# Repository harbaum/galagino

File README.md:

# Galagino - ESP32 Arcade Emulator

Play Galaga, Pac-Man, Donkey Kong, Frogger, Digdug and 1942 on the ESP32

## New and improved versions

Since Galagino was started in 2023 many developers have updated
and improved this project and these successors have long left this
original Galagino behind.

I recommend you check the following versions as well:

  * [GalaginoPlus](https://github.com/VirtualClaudioBoy/GalaginoPlus) featuring an impressive 43 games and most other third party contributions
  * [Speckhoilers Galagino](https://github.com/speckhoiler/galagino) increasing the number of supported games to 30!!
  * [Galagino3](https://github.com/SurvivalHacking/galagino3) adding several new games, supporting an OLED for the marquee and enhancing joystick support as well as adding new games
  * [Another Galagino](https://github.com/galagino/galagino) adding new games and support for more display types
  * ... and various other great ports and contributions ...

## Original Galagino from 2023

[Pac-Man](https://en.wikipedia.org/wiki/Pac-Man),
[Galaga](https://en.wikipedia.org/wiki/Galaga) and
[Donkey Kong](https://en.wikipedia.org/wiki/Donkey_Kong_(video_game)) are three of the most
iconic arcade machines of all times and are listed on places #1 to #3
on the [Killer List of Video Games](http://www.klov.net).

Especially Pac-Man and Galaga have been remade and emulated many
times. So far the cheapest and smallest system able to do a faithful
emulation of the original arcade machines was the raspberry pi. But
even the much cheaper ESP32 should be able to easily emulate a machine
from the early ’80s, shouldn't it?

Well, things are not that easy. The Galaga arcade was driven by three
Z80 CPUs, each running at 3Mhz. Additionally the arcade machine
included two more CPUs, one for button and coin handling and one for audio
support. And finally the hardware itself had dedicated support
for simple wavetable audio, tilemap graphics and up to 64 sprites.
The video resultion was 224 by 288 pixels.

The ESP32 on the other hand
comes with two cores running at 240MHz. But it lacks dedicated video
hardware. Emulating the various CPUs as well as the handling of
audio and graphics turned out to be challenging for the ESP32.

Cheap TFT screens with a resolution of 320 by 240 pixels are avaialable
in various sizes from 2.0 inch to 3.2 inch allowing for a very small
and cheap *galagino* setup.

These small displays usually allow for SPI clock rates of up to 40MHz
allowing for a max screen refresh rate of ~30Hz. This is exactly half
the refresh rate of the original arcade machine. 30Hz is sufficient
for a very fluid gameplay. However, with displays coping with 80MHz
SPI clock, Galagino will run at full 60Hz refresh.

## Youtube videos

* [First Galaga Emulation test ](https://www.youtube.com/shorts/LZRI6izM8XM)
* [Sound and Starfield working](https://www.youtube.com/shorts/8uNSv0aRtgY)
* [Galaga is finally playable](https://www.youtube.com/shorts/wqnJzOAAths)
* [Pac-Man on Galagino](https://www.youtube.com/shorts/F4-XiiPwG1c)
* [Donkey Kong on Galagino](https://www.youtube.com/shorts/KROFJ0Rtj0w)
* [Boot menu](https://www.youtube.com/shorts/_PJyn06yrtg)
* [Cardboard cabinet prototype](https://youtube.com/shorts/vverV4NphlQ)
* [Finished plywood cabinet](https://youtube.com/shorts/a3-wctRAIds)
* [John Bradnam's 3D printed case](https://www.youtube.com/watch?v=p29Yvht4jSI)
* [Frogger on Galagino](https://youtube.com/shorts/LrBkN1pu7yE)
* [Digdug on Galagino](https://youtube.com/shorts/fmQmfKEhVy4)

## Hardware

### Original Hardware
The hardware is built around one of those cheap ESP32 development
boards like the ESP32 Devkit V4 depicted in the images below. The
components needed for the breadboard setup are listed below. If you
plan to build the [cabinet](hardware/cabinet) instead you might want
to make sure you [order the exact parts](./hardware) that
aren't only electrically compatible but also mechanically.

* ESP32 development board (e.g. [Devkit V4](https://www.espressif.com/en/products/devkits/esp32-devkitc))
* A 320x240 SPI TFT screen (no touch needed)
  * Either a ILI9341 based screen as depicted, or
  * a ST7789 based screen with 320x240 pixels
* An audio amplifier and speaker
  * e.g. a [PAM8302A](https://www.adafruit.com/product/2130) and a 3W speaker (as seen in the photos), or
  * a [Keyestudio SC8002B](https://www.keyestudio.com/products/keyestudio-sc8002b-audio-power-amplifier-speaker-module-for-arduino-player), or similar 
* five push buttons, or
* one push button and a five way joystick breakout (for Pac-Man and Donkey Kong)
* breadboard and wires

The entire setup should be connected as depicted below. The Devkit is
too wide for the breadboard leaving no space above it to connect
wires. Thus the wires going to the top pin row of the Devkit are
placed underneath the DevKit with the connections done as shown in the
image below. See [galagino/config.h](galagino/config.h) for the button
mappings.

[PDF](images/galagino_bb.pdf)

This setup with five buttons works fine for Galaga since there is no
vertical movement in the game that requires a joystick. A joystick is
needed for Pac-Man and Donkey Kong. The joystick based setup would
then be wired in the following way:

[PDF](images/galagino_5way_bb.pdf)

### "Cheap Yellow Display"
The ESP32-2432S028R A.K.A. the [Cheap Yellow Display](https://github.com/witnessmenow/ESP32-Cheap-Yellow-Display) is an ESP32 Board that comes with the majority of hardware required to build a Galagino device.

Hardware Needed:
- Cheap Yellow Display
- [A Nintendo Wii nunchuck and adaptor](hardware/NUNCHUCK.MD) - This can be connected to the JST connector labled "CN1" with the cable included with the display
- (or) a [Nintento Switch Pro Controller](hardware/BLUEPAD32.MD) or [similar](https://github.com/ricardoquesada/bluepad32)
- A speaker - This can be attached to the display with a 1.25mm JST connector to the connector labled "SPEAK" (or soldered)

Note: The `Start` button is connected to the "boot" button on the board.

To get the project working on the Cheap Yellow Display, just uncomment the `#define CHEAP_YELLOW_DISPLAY_CONF` line in [galagino/config.h](galagino/config.h)

## Software

**Important notice 1:** You really need to use the Arduino IDE as it
provides the optimization settings required for sufficient
perfgormance of Galaga and Digdug by default. E.g. PlatformIO doesn't
seem to enable enough optimization.

**Important notice 2:** I2S/DAC support seems to be [broken in the
ESP32 board package version 2.0.10 and
up](https://github.com/espressif/arduino-esp32/issues/8467). Please
use ESP32 board package 2.0.9 or older for a clean sound.

The software consists of three parts:

* The [Galagino specific code](galagino/) contained in this repository
* The orignal ROM files
    * [Galaga (Namco Rev. B ROM)](https://www.bing.com/search?q=galaga+namco+b+rom)
    * [Pac-Man (Midway)](https://www.bing.com/search?q=pacman+midway+arcade+rom)
    * [Donkey Kong (US set 1)](https://www.bing.com/search?q=donkey+kong+arcade+rom)
    * [Frogger](https://www.bing.com/search?q=frogger+arcade+rom)
    * [Digdug](https://www.bing.com/search?q=digdug+arcade+rom)
    * [1942](https://www.bing.com/search?q=1942+arcade+rom)	
* A [Z80 software emulation](https://fms.komkon.org/EMUL8/Z80-081707.zip) by [Marat Fayzullin](https://fms.komkon.org/)

Galagino uses code that is not freely available and thus not included in this
repository. Preparing the firmware thus consists of a few additional steps:

* The ROM files have to be placed in the [roms directory](roms/), together with the ZIP file containing the Z80 emulator.
* A set of [python scripts](romconv/) is then being used to convert and
 patch the ROM data and emulator code and to include the resulting code into the
galagino sketch directory.
* The same scripts are afterwards being used to convert [audio sample files](./samples) into the desired format.

The [ROM conversion](./romconv) as well as the [audio sample
conversion](./samples) create a whole bunch of additional files in the
[galagino directory](./galagino). Please check the README's in the
[romconv](./romconv) and [samples](./samples) directories for further
instructions.

With all these files in place, the galagino.ino sketch can be loaded
into the [Arduino IDE](https://docs.arduino.cc/software/ide-v2). The
Arduino IDE must have the [ESP32 board support](https://docs.espressif.com/projects/arduino-esp32/en/latest/installing.html)
installed and the appropriate board like e.g. the
*ESP32 Dev Module* should be selected. Finally the default core used
by Arduino should be 1 (this is the default) as Galagino will use core 0
for audio and video emulation. Furthermore the FastLED library should
be installed to support the LEDs in the [cabinets marquee](./hardware/cabinet).
LED support can be disabled in the configuration if no LEDs are going to be installed.

## Configuration

The Galagino code can be configured through the [galagino/config.h](galagino/config.h)
file. This is also the place where it's possible to choose between the ILI9341
controller (default) and the ST7789.

Also the pin assignment can be adjusted as well as the TFT SPI clock or the
use of LEDs for the marquee.

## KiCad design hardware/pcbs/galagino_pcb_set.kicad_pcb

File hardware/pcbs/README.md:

# Galagino PCB set

The Galagino PCB set is meant to make assembly much easier.
It consists of three PCBs. One is for the display, one for the
ESP32 and one for the joystick. 

The joystick comes with a freecad design for matching plastic parts:

- The main cover [controlboard_base.stl](controlboard_base.stl)
- The actuator that pusges against the direction buttons [controlboard_actuator.stl](controlboard_actuator.stl)
- The joystick control knob [controlboard_knob.stl](controlboard_knob.stl)
- Two raiser to be mounted below the start and fire button [btn_raiser.stl](btn_raiser.stl)

The joystick uses standard 6x6mm through-hole buttons with the legs
bent 90 deg outwards to go through the PCB and the other legs being
cut.

[PDF](schematic.pdf)

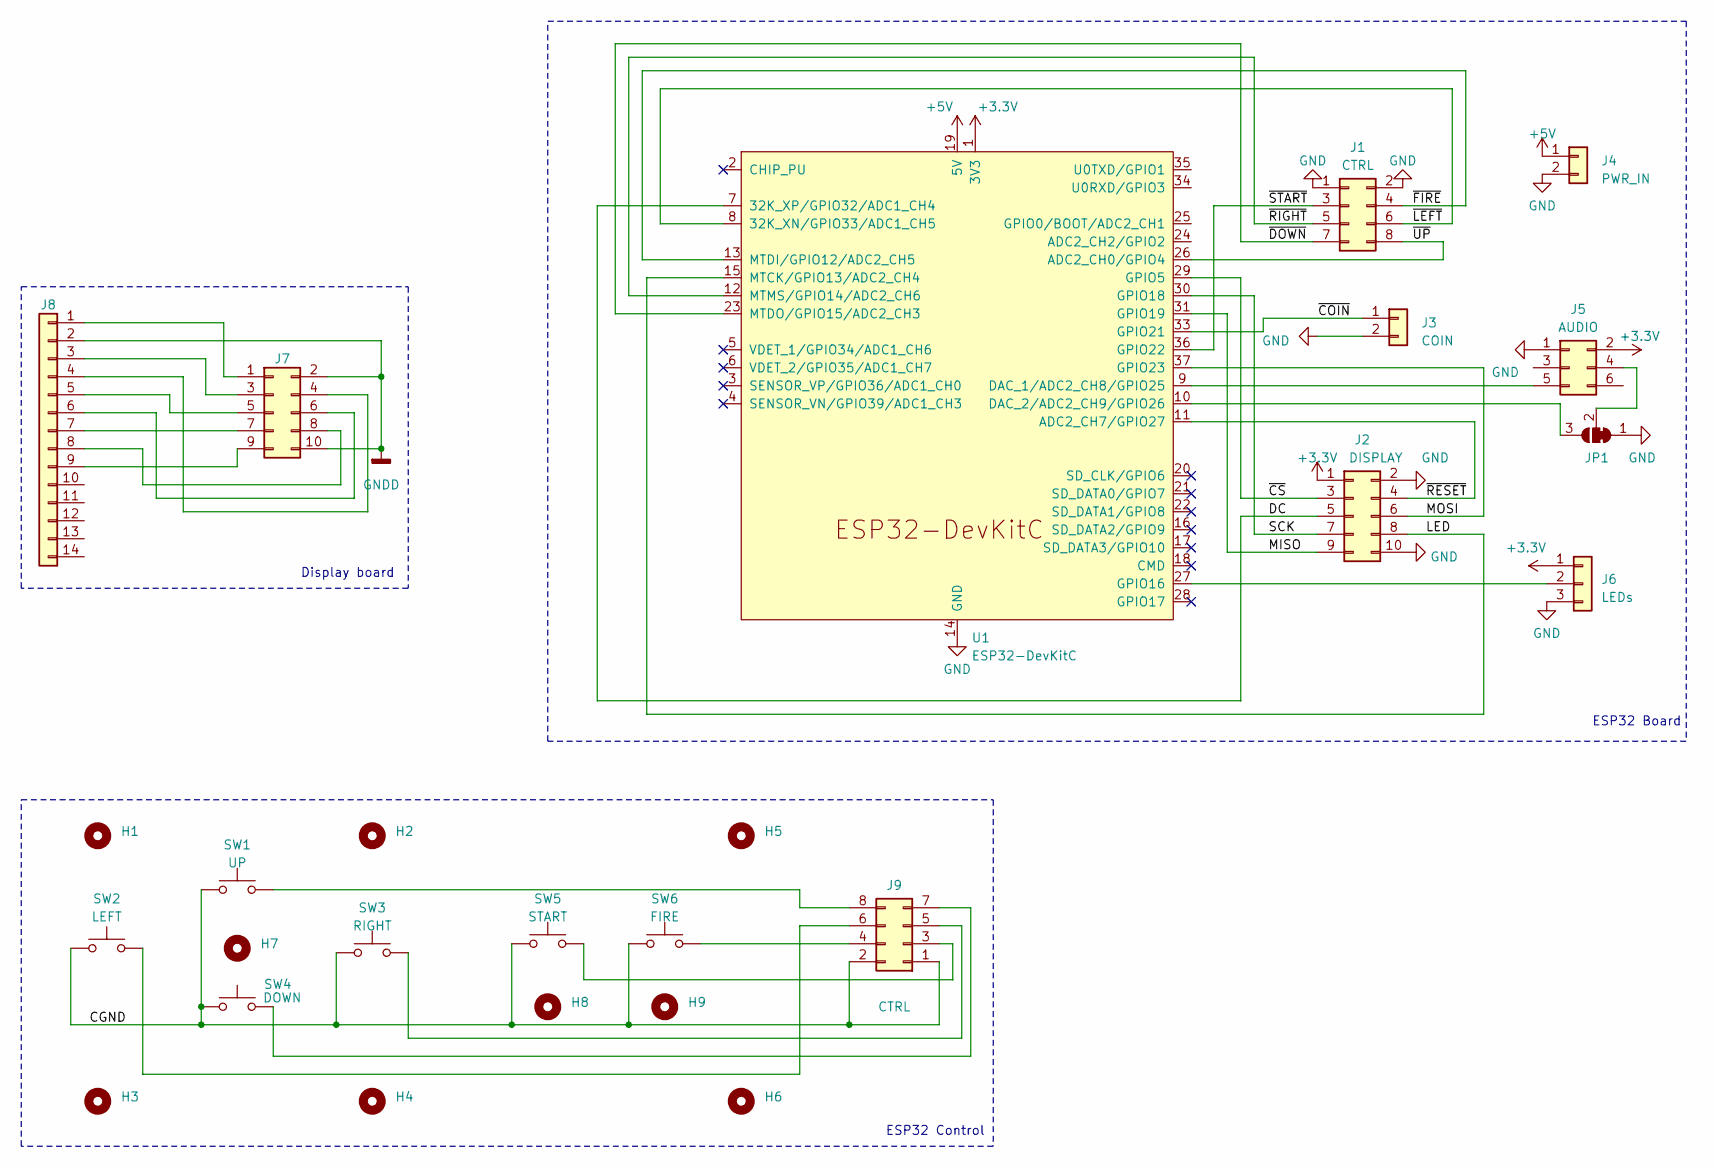
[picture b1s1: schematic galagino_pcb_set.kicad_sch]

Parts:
H1, H2, H3, H4, H5, H6, H8, H9: MountingHole; MountingHole_2.2mm_M2_ISO7380
H7: MountingHole; MountingHole_5mm
J1, J9: CTRL; PinHeader_2x04_P2.54mm_Vertical
J2, J7: DISPLAY; PinHeader_2x05_P2.54mm_Vertical
J3: COIN; PinHeader_1x02_P2.54mm_Vertical
J4: PWR_IN; PinHeader_1x02_P2.54mm_Vertical
J5: AUDIO; PinHeader_2x03_P2.54mm_Vertical
J6: LEDs; PinHeader_1x03_P2.54mm_Vertical
J8: Conn_01x14; PinSocket_1x14_P2.54mm_Vertical
JP1: DIFF; SolderJumper-3_P1.3mm_Open_RoundedPad1.0x1.5mm
SW1: UP; btn_4.3mm_THT
SW2: LEFT; btn_4.3mm_THT
SW3: RIGHT; btn_4.3mm_THT
SW4: DOWN; btn_4.3mm_THT
SW5: START; SW_PUSH_6mm_H9.5mm
SW6: FIRE; SW_PUSH_6mm_H9.5mm
U1: ESP32-DevKitC

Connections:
+3.3V: J2.1, J5.2, J6.1, U1.1 (3V3)
+5V: J4.1, U1.19 (5V)
/CGND: J9.1, J9.2, SW1.1, SW2.1, SW3.1, SW4.1, SW5.1, SW6.1
/DC: J2.5, U1.7 (32K_XP/GPIO32/ADC1_CH4)
/LED: J2.8, U1.15 (MTCK/GPIO13/ADC2_CH4)
/MISO: J2.9, U1.31 (GPIO19)
/MOSI: J2.6, U1.37 (GPIO23)
/SCK: J2.7, U1.30 (GPIO18)
/~COIN: J3.1, U1.33 (GPIO21)
/~CS: J2.3, U1.29 (GPIO5)
/~DOWN: J1.7, U1.23 (MTDO/GPIO15/ADC2_CH3)
/~FIRE: J1.4, U1.13 (MTDI/GPIO12/ADC2_CH5)
/~LEFT: J1.6, U1.8 (32K_XN/GPIO33/ADC1_CH5)
/~RESET: J2.4, U1.11 (ADC2_CH7/GPIO27)
/~RIGHT: J1.5, U1.12 (MTMS/GPIO14/ADC2_CH6)
/~START: J1.3, U1.36 (GPIO22)
/~UP: J1.8, U1.26 (ADC2_CH0/GPIO4)
GND: J1.1, J1.2, J2.2, J2.10, J3.2, J4.2, J5.1, J6.3, JP1.1 (A), U1.14 (GND), U1.32 (GND), U1.38 (GND)
GNDD: J7.2, J7.10, J8.2
unnamed: J5.4, JP1.2 (C)
unnamed: J5.5, U1.9 (DAC_1/ADC2_CH8/GPIO25)
unnamed: J6.2, U1.27 (GPIO16)
unnamed: J7.1, J8.1
unnamed: J7.3, J8.3
unnamed: J7.4, J8.4
unnamed: J7.5, J8.5
unnamed: J7.6, J8.6
unnamed: J7.7, J8.7
unnamed: J7.8, J8.8
unnamed: J7.9, J8.9
unnamed: J9.3, SW5.2
unnamed: J9.4, SW6.2
unnamed: J9.5, SW3.2
unnamed: J9.6, SW2.2
unnamed: J9.7, SW4.2
unnamed: J9.8, SW1.2
unnamed: JP1.3 (B), U1.10 (DAC_2/ADC2_CH9/GPIO26)

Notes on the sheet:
ESP32 Board
ESP32 Control
Display board

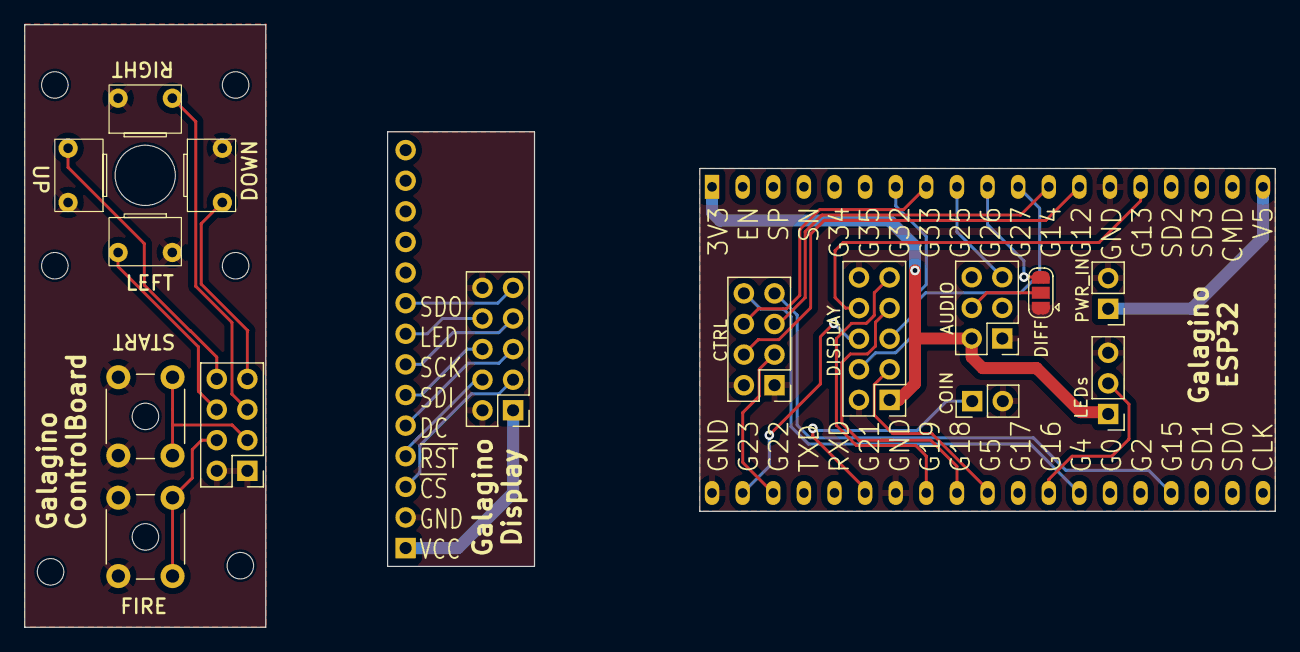
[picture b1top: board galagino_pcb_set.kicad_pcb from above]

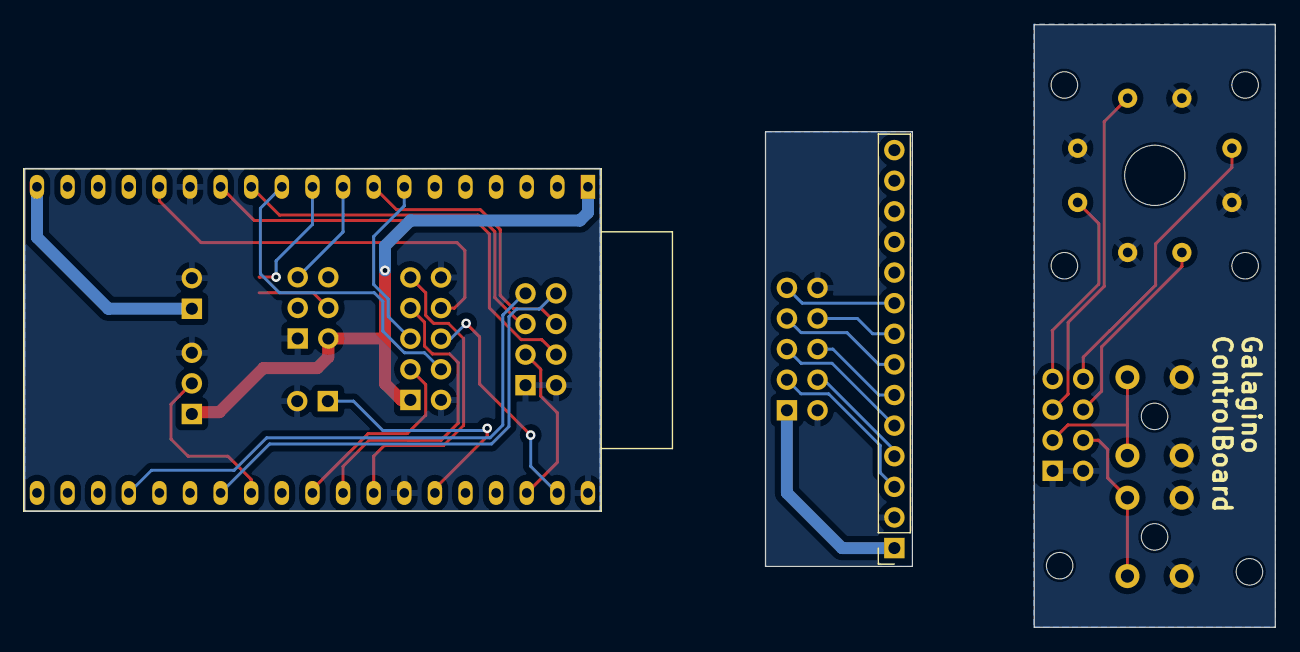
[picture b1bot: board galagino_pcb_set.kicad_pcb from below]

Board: 2 copper layers, 103.8 x 50.0 mm, 26 parts (2 on the bottom side), 37 nets.

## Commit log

2023-01-15 Add readme
2023-01-15 Add code and code converters
2023-01-15 Add teaser gif
2023-01-15 Add fritzing scheme
2023-01-15 Youtube links
2023-01-15 Added photo
2023-01-15 Hardware description
2023-01-15 Autogenerated files
2023-01-16 Build instructions
2023-01-27 typo: 80's → ’80s
2023-01-27 Add link to donkey kong video
2023-01-27 Add 5 way joystick setup
2023-01-28 Add Pac-Man and Donkey Kong
2023-01-28 Fix image size
2023-01-28 ROM info
2023-01-28 ROM description
2023-01-28 Fix dkong sprite instructions
2023-01-28 Add missing spring sample
2023-01-28 Fix typos
2023-01-28 Temporary hack around issue #3
2023-01-29 Fix colormap masking, fixes #4
2023-01-29 Cleaning fritzing
2023-01-31 Fix i2s audio for 2.0.6
2023-02-04 Add some dkong spounds an implement video DMA as described in #10
2023-02-04 Allow for 60 hz video if hardware copes with that
2023-02-04 Link to VGA ESP32
2023-02-05 Add option to combine coin and start button. Implements #8
2023-02-05 Include optional patches for faster galaga boot. Implementing #9
2023-02-11 Add Donkey Kong 8048 audio CPU
2023-02-11 Mention DK audio CPU ROM
2023-02-11 Add missing Galaga sound sample
2023-02-11 Fix READMEs
2023-02-12 Balance dkong volumes and mix samples
2023-02-12 Reset to menu when coin is pressed > 1 sec
2023-02-12 Reduce Dkong walk volume
2023-02-13 Update README and more animated GIFs
2023-02-13 Fix dkong wikipedia url
2023-02-14 Use three dkong walk sound variants for more authentic walk sound
2023-02-19 Drive tft backlight
2023-02-19 Disable backlight before reset
2023-02-20 Add tft backlight control
2023-03-08 Add control board CAD files
2023-03-09 Add photo
2023-03-22 Marquee and coin button CAD files
2023-03-22 Add assembly instructions
2023-03-22 Fix readme
2023-03-22 Fix display orientation
2023-03-22 step by step instructions
2023-03-23 Lasercut cabinet
2023-03-25 More assembly instructions
2023-03-29 Add case plan
2023-03-29 Fix rear part
2023-03-29 Clarify instructions
2023-03-29 Cabinet Assembly descriptions
2023-03-29 Resize images
2023-03-30 Partial master attract mode
2023-03-30 Update readmes
2023-03-30 Part list
2023-03-31 Document marquee part
2023-03-31 coinbutton mounting
2023-03-31 Photo of parts
2023-04-21 Add some generated files
2023-04-23 Controlboard wireing
2023-04-23 Update controlboard files
2023-04-23 more wiring instructions
2023-04-23 joystick assembly
2023-05-25 Link to 3d printed case
2023-05-31 Add frogger support to conversion scripts
2023-05-31 Add frogger logo for menu
2023-05-31 Add frogger emulation code and allow for scrolling menu
2023-05-31 Add converted frogger logo
2023-05-31 Frogger rom description
2023-05-31 Script bug fixes
2023-05-31 Typo
2023-05-31 Link to frogger video
2023-06-16 Digdug ROM handling
2023-06-16 Add digdug emulation
2023-06-16 Mention new games
2023-06-16 Digdug ROM description
2023-06-17 Fix #19
2023-06-18 Move more code into machine specific header
2023-06-27 Adding support for CYD, non standard SPI pins and nunchuck
2023-06-27 Adding Audio Support for the CYD
2023-06-29 Adding Image for CYD
2023-06-29 Adding info about the start button
2023-06-29 Adding CYD image to README.md
2023-06-29 Adding instructions to install the nunchuck library
2023-06-30 Fix for default setup
2023-07-06 Allow custom memory access control for CYD
2023-07-08 Add 1942 rom conversion
2023-07-09 Fix #23
2023-07-09 Include 1942 roms into gitignore
2023-07-12 1942 ROM set
2023-07-12 1942 logo
2023-07-12 Add custom StepZ80 for Digdug
2023-07-12 Add 1942 support
2023-07-12 Fix typo
2023-07-12 1942 rom info
2023-07-12 Add screenshots
2023-07-12 Crop screenshots
2023-07-27 Mention issues with PlatformIO and ESP board package > 2.0.9
2023-07-28 Fix audio channel mapping
2023-07-29 Workaround byte order bug in ESP IDF
2023-07-29 Link to sound issues
2023-07-29 Implement workaround for #27
2023-08-03 Fixed conv_win.sh (Issue #29) and updated readme for Rom conversion
2023-11-01 Adding Pre-processor logic for left channel devices
2023-12-26 Add PCB setup
2024-02-02 Add nunchuck button C handling as COIN/START alternative.
2024-02-14 Reworked code for more universal nintendo-input, added functionality
    This commit changes the following:
    1. replace Nunchuk.h with Nintendo.h
    2. add Classic Controller with D-pad, a-button=FIRE, -button(select) = COIN,+button (start) = START, home-button=reset_emulation
    3. enhance Nunchuk capabilities: Z-button= FIRE, C-button=COIN, Z and C together=START, Joystick DOWN+Z+C=reset_emulation
    I know this pretty much reverts D0023R's last pullrequest but IMHO it makes things more flexible and more better! ;) Next step I will work on is autodetection of Nintendo-controller.
2024-02-19 Add autodetection for Nintendo controllers, add DPAD and Joystick Option for classic controller
    1. If you enable NINTENDO_INPUT in config.h, on bootup of the machine, the controller is detected automagically. Currently supported: Nunchuk and Classic controller (don't see any value in having gui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
    2. Added #define CLASSIC_DPAD and CLASSIC_LJOY
    You can use either of them or both on the Classic controller. You have to define at least one. If not, you will receive a compiler error message when building
2024-03-03 Update control board case
2024-03-03 Add btn_raiser
2024-03-03 Update pcb readme
2024-03-05 Deepen screw head holes
2024-03-06 Case variant with cuts for battery charger and switch
2024-03-06 Moved power switch up a little bit
2024-03-11 Update cabinet for use with a battery
2024-03-11 Desciption of battery usage
2025-02-22 Fix #45 inverted display.
2026-04-04 Fix 1942 audio distortion and add master volume control
    1942 has 2 AY chips (6 channels) but AY_VOL was set to 10, producing
    a max amplitude of 900 before the *64 scaler. This overflowed the
    signed short range (32,767), causing severe clipping and distortion.
    Reduced AY_VOL to 4 to keep within range.
    Added MASTER_VOLUME define in config.h to allow tuning the overall
    audio output level (range 1-64, default 64).
2026-04-04 Fix Galaga fire edge detection and menu return
    Galaga: the Namco 06xx 3-byte polling cycle read buttons and updated
    prev_mask on every byte, so fire/coin/start edges were frequently
    consumed on byte 0 (credit byte) before the byte that encodes them.
    Sample buttons once at namco_cnt==0 and latch the fire edge for the
    whole cycle so byte 1 always reports it reliably.
    buttons_get: the BUTTON_EXTRA detection was wrapped in nested
2026-04-04 Minor correctness fixes
    setCpuFrequencyMhz takes MHz, not Hz — 240000000 is rejected by the
    ESP32 core as an invalid frequency and silently does nothing. Passes
    240 so the call actually works (the CPU is already at 240MHz on boot,
    so no behavioral change).
    Pac-Man sound register write had a precedence bug: "a != b & 0x0f"
    parses as "(a != b) & 0x0f" because != binds tighter than bitwise &.
2026-06-23 feat: add Bluepad32 support for Nintendo Switch Pro Controller
    - Enable BLUE32_CONTROLLER_INPUT in config.h to support Bluetooth controllers.
    - Integrate Bluepad32 API with connection/disconnection callbacks.
    - Update buttons_get() to merge Bluetooth input (D-Pad/Stick/Buttons) with physical arcade controls.
    - Implement intelligent mapping:
    - Left/Right/Up/Down mapped to both D-Pad and Analog Stick (with deadzone).
    - Plus (+) and Minus (-) mapped to Start and Coin respectively.
